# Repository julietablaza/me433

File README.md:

# me433

[HW2 LED blink demo video](https://drive.google.com/file/d/15Y7G__UTLzQ2tHiy7Zud-tasaBCwR0PT/view?usp=sharing)

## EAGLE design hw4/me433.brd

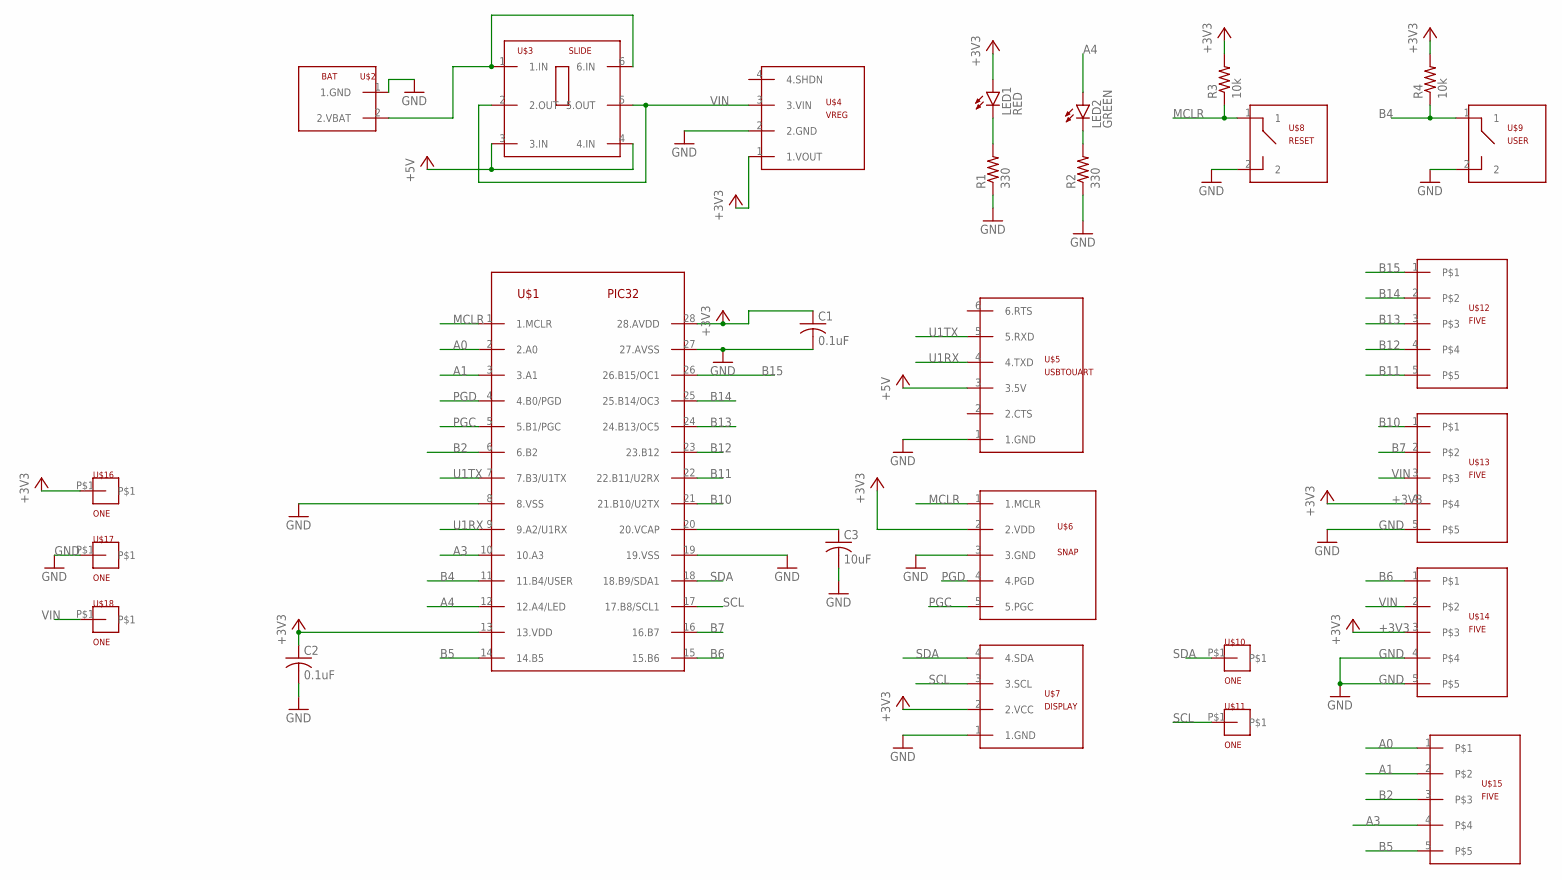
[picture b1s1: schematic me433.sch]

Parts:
C1, C2: 0.1uF; C025-024X044
C3: 10uF; C025-024X044
LED1: RED; LED3MM
LED2: GREEN; LED3MM
R1, R2: 330; 0207/7
R3, R4: 10k; 0207/7
U$1: PIC32; DIL28-3
U$2: BAT
U$3: SLIDE
U$4: VREG; VOLTAGEREG
U$5: USBTOUART
U$6: SNAP
U$7: DISPLAY
U$8: RESET; BUTTON
U$9: USER; BUTTON
U$10, U$11, U$16, U$17, U$18: ONE
U$12, U$13, U$14, U$15: FIVE

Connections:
+3V3: C1.1, C2.1, LED1.A, R3.2, R4.2, U$1.13 (13.VDD), U$1.28 (28.AVDD), U$4.1 (1.VOUT), U$6.2 (2.VDD), U$7.2 (2.VCC), U$13.4, U$14.3, U$16.P$1
+5V: U$3.3 (3.IN), U$3.4 (4.IN), U$5.3 (3.5V)
A0: U$1.2 (2.A0), U$15.1
A1: U$1.3 (3.A1), U$15.2
A3: U$1.10 (10.A3), U$15.4
A4: LED2.A, U$1.12 (12.A4/LED)
B2: U$1.6 (6.B2), U$15.3
B4: R4.1, U$1.11 (11.B4/USER), U$9.1
B5: U$1.14 (14.B5), U$15.5
B6: U$1.15 (15.B6), U$14.1
B7: U$1.16 (16.B7), U$13.2
B10: U$1.21 (21.B10/U2TX), U$13.1
B11: U$1.22 (22.B11/U2RX), U$12.5
B12: U$1.23 (23.B12), U$12.4
B13: U$1.24 (24.B13/OC5), U$12.3
B14: U$1.25 (25.B14/OC3), U$12.2
B15: U$1.26 (26.B15/OC1), U$12.1
GND: C1.2, C2.2, C3.2, R1.1, R2.1, U$1.8 (8.VSS), U$1.19 (19.VSS), U$1.27 (27.AVSS), U$2.1 (1.GND), U$4.2 (2.GND), U$5.1 (1.GND), U$6.3 (3.GND), U$7.1 (1.GND), U$8.2, U$9.2, U$13.5, U$14.4, U$14.5, U$17.P$1
MCLR: R3.1, U$1.1 (1.MCLR), U$6.1 (1.MCLR), U$8.1
unnamed: U$2.2 (2.VBAT), U$3.1 (1.IN), U$3.6 (6.IN)
unnamed: LED1.K (C), R1.2
unnamed: C3.1, U$1.20 (20.VCAP)
unnamed: LED2.K (C), R2.2
PGC: U$1.5 (5.B1/PGC), U$6.5 (5.PGC)
PGD: U$1.4 (4.B0/PGD), U$6.4 (4.PGD)
SCL: U$1.17 (17.B8/SCL1), U$7.3 (3.SCL), U$11.P$1
SDA: U$1.18 (18.B9/SDA1), U$7.4 (4.SDA), U$10.P$1
U1RX: U$1.9 (9.A2/U1RX), U$5.4 (4.TXD)
U1TX: U$1.7 (7.B3/U1TX), U$5.5 (5.RXD)
VIN: U$3.2 (2.OUT), U$3.5 (5.OUT), U$4.3 (3.VIN), U$13.3, U$14.2, U$18.P$1

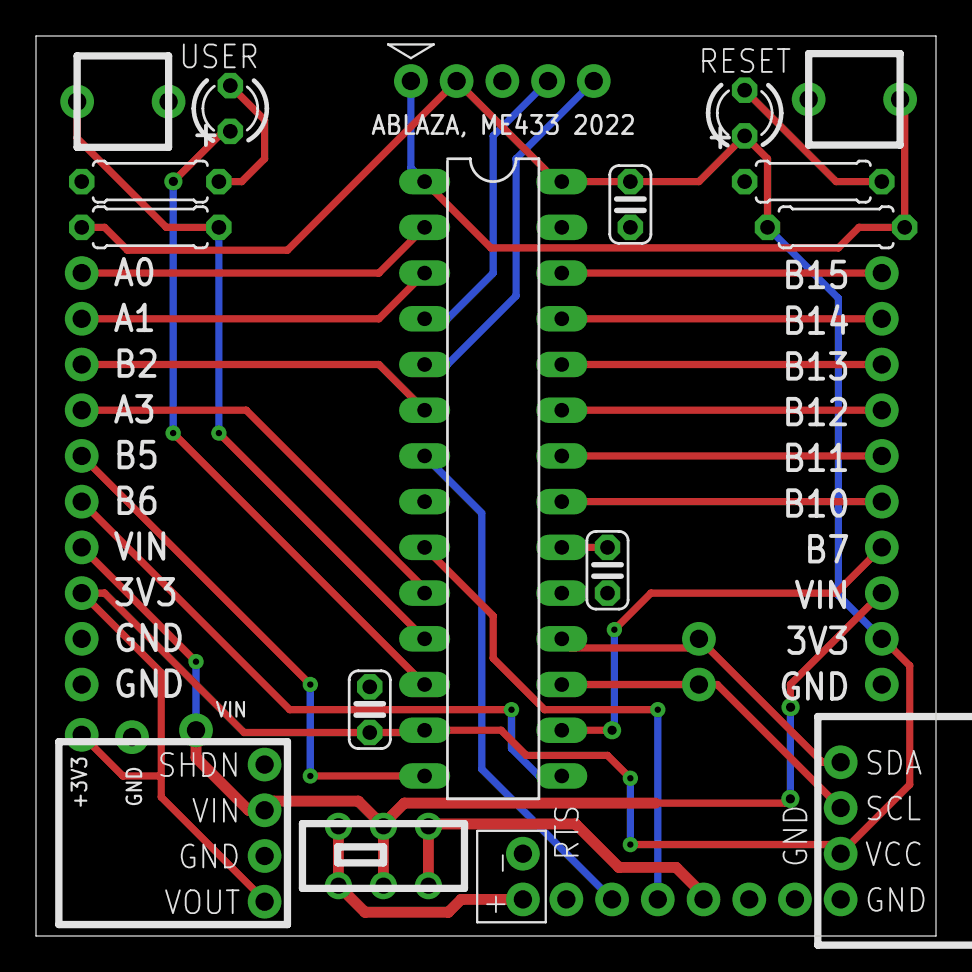
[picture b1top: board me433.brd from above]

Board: 2 copper layers, 50.0 x 50.0 mm, 27 parts (0 on the bottom side), 30 nets.

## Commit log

2022-04-07 main.c, circuit diagram, breadboard
2022-04-07 demo video link
2022-05-02 created library
2022-05-02 made schematic
2022-05-04 made board layout
2022-05-24 hw3 - UART
2022-05-25 created hw5 folder
2022-05-25 initial SPI
